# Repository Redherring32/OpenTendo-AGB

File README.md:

# OpenTendo Game Boy Advance (OpenGBA)

This is an open source recreation of the AGB-CPU-01 board. This was a joint effort between Redherring32 and Bucket Mouse (Mousebitelabs) - initial board scans, copper tracing, and footprint generation were done by Redherring32; schematic and symbol generation, PCB copper cleanup, and silkscreen were done by Bucket Mouse. This is a close to 1:1 recreation of the original AGB-CPU-01 circuit board - some liberties were taken here and there to ensure ease of manufacturability (namely, 6 mil spacing) and to improve aesthetics (most vias are *tented* rather than untented).

## File Structure

**Board Files**: contains the schematics and PCB files for KiCad 9.0

**Footprints/OpenTendo-AGB.pretty**: component footprints for KiCad 9.0

**Symbols**: component symbols for KiCad 9.0

**Bill_of_Materials.csv**: a list of components and component values for each part on the board (see [this site](https://docs.google.com/spreadsheets/d/17RfgOaR-P8M0cC5BojwuY52GbZUefLFm82To7ja963o/edit?gid=1605207223#gid=1605207223) for some alternatives)

**Gerbers.zip**: files used to order circuit boards from manufacturers (JLCPCB, PCBway, etc.)

## Board Characteristics and Order Information

The zipped folder contains all the gerber files for this board. The following options **must** be chosen when ordering boards for yourself.

- Thickness: 1.0mm
- Surface Finish: ENIG

## License
<br />This work is licensed under a <a rel="license" href="http://creativecommons.org/licenses/by-sa/4.0/">Creative Commons Attribution-ShareAlike 4.0 International License</a>. You are able to copy and redistribute the material in any medium or format, as well as remix, transform, or build upon the material for any purpose (even commercial) - but you **must** give appropriate credit, provide a link to the license, and indicate if any changes were made.

©Redherring32 2023-2026

©MouseBiteLabs 2026

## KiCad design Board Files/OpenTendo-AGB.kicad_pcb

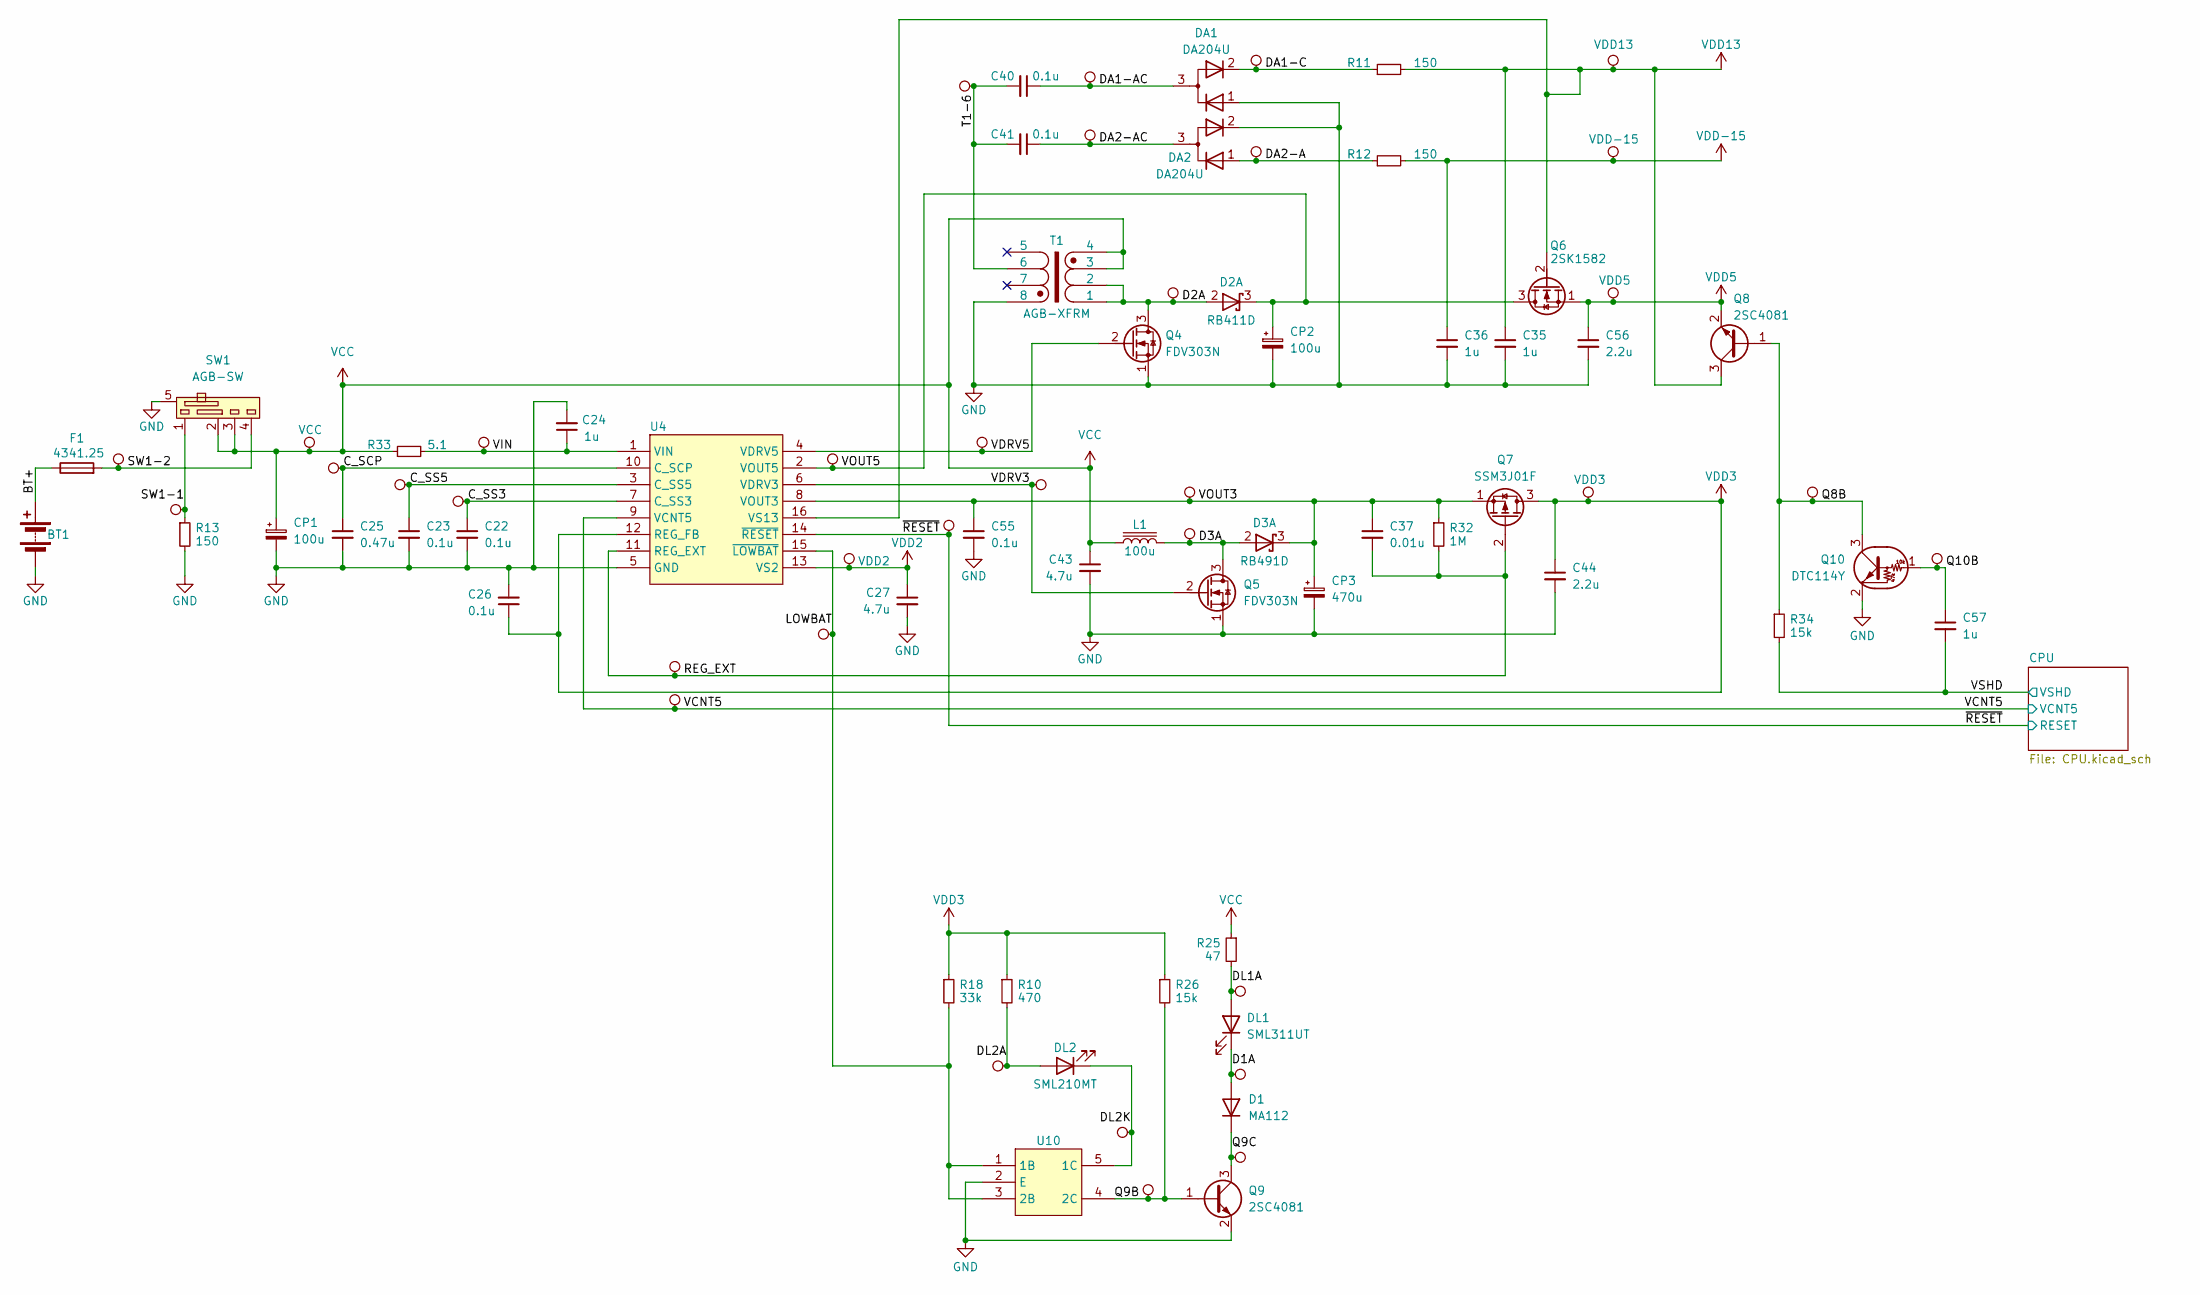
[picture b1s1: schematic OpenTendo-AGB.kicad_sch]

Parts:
BT1: Battery
C22, C23, C26, C40, C41, C55: 0.1u; C_0402_1005Metric
C24, C57: 1u; C_0603_1608Metric
C25: 0.47u; C_0603_1608Metric
C27, C43: 4.7u; C_0805_2012Metric
C35, C36: 1u; C_0805_2012Metric
C37: 0.01u; C_0402_1005Metric
C44, C56: 2.2u; C_0805_2012Metric
CP1: 100u; CP_Elec_5x5.3
CP2: 100u; C_Elec_6.3x5.8
CP3: 470u; C_Elec_8x10.2
D1: MA112; Diode
D2: RB411D; SOT-23
D3: RB491D; SOT-23
DA1, DA2: DA204U; SOT-323
DL1: SML311UT; LED_0603_1608Metric
DL2: SML210MT; LED_0603_1608Metric
F1: 4341.25; Fuse_0603_1608Metric
L1: 100u; Inductor
Q4, Q5: FDV303N; SOT-23
Q6: 2SK1582; SOT-23
Q7: SSM3J01F; SOT-23
Q8, Q9: 2SC4081; SOT-323
Q10: DTC114Y; SOT-323
R10: 470; R_0402_1005Metric
R11, R12, R13: 150; R_0402_1005Metric
R18: 33k; R_0402_1005Metric
R25: 47; R_0402_1005Metric
R26, R34: 15k; R_0402_1005Metric
R32: 1M; R_0402_1005Metric
R33: 5.1; R_0402_1005Metric
SW1: AGB-SW; Power Switch
T1: AGB-XFRM; Coil
TP10: VOUT3; TestPoint_Pad_D1.0mm_VIA
TP11: VDRV3; TestPoint_Pad_D1.0mm
TP12: VDD2; TestPoint_Pad_D0.8mm
TP13: VDRV5; TestPoint_Pad_D1.0mm
TP14: VOUT5; TestPoint_Pad_D0.8mm
TP15: ~{RESET}; TestPoint_Pad_D1.25mm_VIA
TP16: D3A; TestPoint_Pad_D1.0mm
TP17: D2A; TestPoint_Pad_D1.0mm_VIA
TP18: DA2-AC; TestPoint_Pad_D0.8mm_VIA
TP19: DA1-AC; TestPoint_Pad_D1.0mm_VIA
TP20: DA2-A; TestPoint_Pad_D0.8mm
TP21: DA1-C; TestPoint_Pad_D0.8mm
TP22: VDD13; TestPoint_Pad_D0.8mm
TP23: VDD-15; TestPoint_Pad_D1.0mm
TP24: VDD5; TestPoint_Pad_D1.0mm
TP25: Q8B; TestPoint_Pad_D0.8mm
TP27: Q10B; TestPoint_Pad_D0.8mm_VIA
TP28: LOWBAT; TestPoint_Pad_D0.8mm
TP29: DL2A; TestPoint_Pad_D0.8mm_VIA
TP30: DL2K; TestPoint_Pad_D0.8mm_VIA
TP31: DL1A; TestPoint_Pad_D0.8mm_VIA
TP32: D1A; TestPoint_Pad_D0.8mm_VIA
TP33: Q9C; TestPoint_Pad_D1.0mm
TP34: Q9B; TestPoint_Pad_D0.8mm
TP83: SW1-2; TestPoint_Pad_D1.25mm
TP84: SW1-1; TestPoint_Pad_D0.8mm
TP85: VCC; TestPoint_Pad_D0.8mm
TP86: C_SCP; TestPoint_Pad_D1.0mm
TP87: C_SS5; TestPoint_Pad_D1.0mm
TP88: C_SS3; TestPoint_Pad_D1.0mm
TP89: VIN; TestPoint_Pad_D0.8mm_VIA
TP90: REG_EXT; TestPoint_Pad_D0.8mm
TP91: VCNT5; TestPoint_Pad_D1.0mm
TP113: VDD3; TestPoint_Pad_D0.8mm
TP116: T1-6; TestPoint_Pad_D1.0mm_VIA
U4: AGB-PMIC; TSSOP-16_4.4x5mm_P0.65mm
U10: UMG3N; SOT-353_SC-70-5

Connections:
/BT+: BT1.1 (+), F1.1
/C_SCP: C25.1, TP86.1, U4.10 (C_SCP)
/C_SS3: C22.1, TP88.1, U4.7 (C_SS3)
/C_SS5: C23.1, TP87.1, U4.3 (C_SS5)
/D1A: D1.2 (A), DL1.1 (K), TP32.1
/D2A: D2.2 (A), Q4.3 (D), T1.1, T1.2, TP17.1
/D3A: D3.2 (A), L1.2, Q5.3 (D), TP16.1
/DA1-AC: C40.1, DA1.3 (common), TP19.1
/DA1-C: DA1.2 (K), R11.1, TP21.1
/DA2-A: DA2.1 (A), R12.1, TP20.1
/DA2-AC: C41.1, DA2.3 (common), TP18.1
/DL1A: DL1.2 (A), R25.2, TP31.1
/DL2A: DL2.2 (A), R10.2, TP29.1
/DL2K: DL2.1 (K), TP30.1, U10.5 (1C)
/LOWBAT: R18.2, TP28.1, U4.15 (~LOWBAT), U10.1 (1B), U10.3 (2B)
/Q8B: Q8.1 (B), Q10.3 (C), R34.1, TP25.1
/Q9B: Q9.1 (B), R26.2, TP34.1, U10.4 (2C)
/Q9C: D1.1 (K), Q9.3 (C), TP33.1
/Q10B: C57.1, Q10.1 (B), TP27.1
/REG_EXT: C37.2, Q7.2 (G), R32.2, TP90.1, U4.11 (REG_EXT)
/SW1-1: R13.1, SW1.1, TP84.1
/SW1-2: F1.2, SW1.4 (2), TP83.1
/T1-6: C40.2, C41.2, T1.6, TP116.1
/VCNT5: TP91.1, U4.9 (VCNT5); also elsewhere on the board
/VDRV3: Q5.2 (G), TP11.1, U4.6 (VDRV3)
/VDRV5: Q4.2 (G), TP13.1, U4.4 (VDRV5)
/VIN: C24.1, R33.2, TP89.1, U4.1 (VIN)
/VOUT3: C37.1, C55.1, CP3.1, D3.3 (K), Q7.1 (S), R32.1, TP10.1, U4.8 (VOUT3)
/VOUT5: CP2.1, D2.3 (K), Q6.3 (D), TP14.1, U4.2 (VOUT5)
/VSHD: C57.2, R34.2; also elsewhere on the board
/~RESET: TP15.1, U4.14 (~RESET); also elsewhere on the board
GND: BT1.2 (-), C22.2, C23.2, C24.2, C25.2, C26.2, C27.2, C35.2, C36.2, C43.2, C44.2, C55.2, C56.2, CP1.2, CP2.2, CP3.2, DA1.1 (A), DA2.2 (K), Q4.1 (S), Q5.1 (S), Q9.2 (E), Q10.2 (E), R13.2, SW1.5 (SH), T1.8, U4.5 (GND), U10.2 (E); also elsewhere on the board
VCC: C43.1, CP1.1, L1.1, R25.1, R33.1, SW1.2 (C), SW1.3 (C), T1.3, T1.4, TP85.1; also elsewhere on the board
VDD2: C27.1, TP12.1, U4.13 (VS2); also elsewhere on the board
VDD3: C26.1, C44.1, Q7.3 (D), R10.1, R18.1, R26.1, TP113.1, U4.12 (REG_FB); also elsewhere on the board
VDD5: C56.1, Q6.1 (S), Q8.2 (E), TP24.1; also elsewhere on the board
VDD13: C35.1, Q6.2 (G), Q8.3 (C), R11.2, TP22.1, U4.16 (VS13); also elsewhere on the board
VDD-15: C36.1, R12.2, TP23.1; also elsewhere on the board

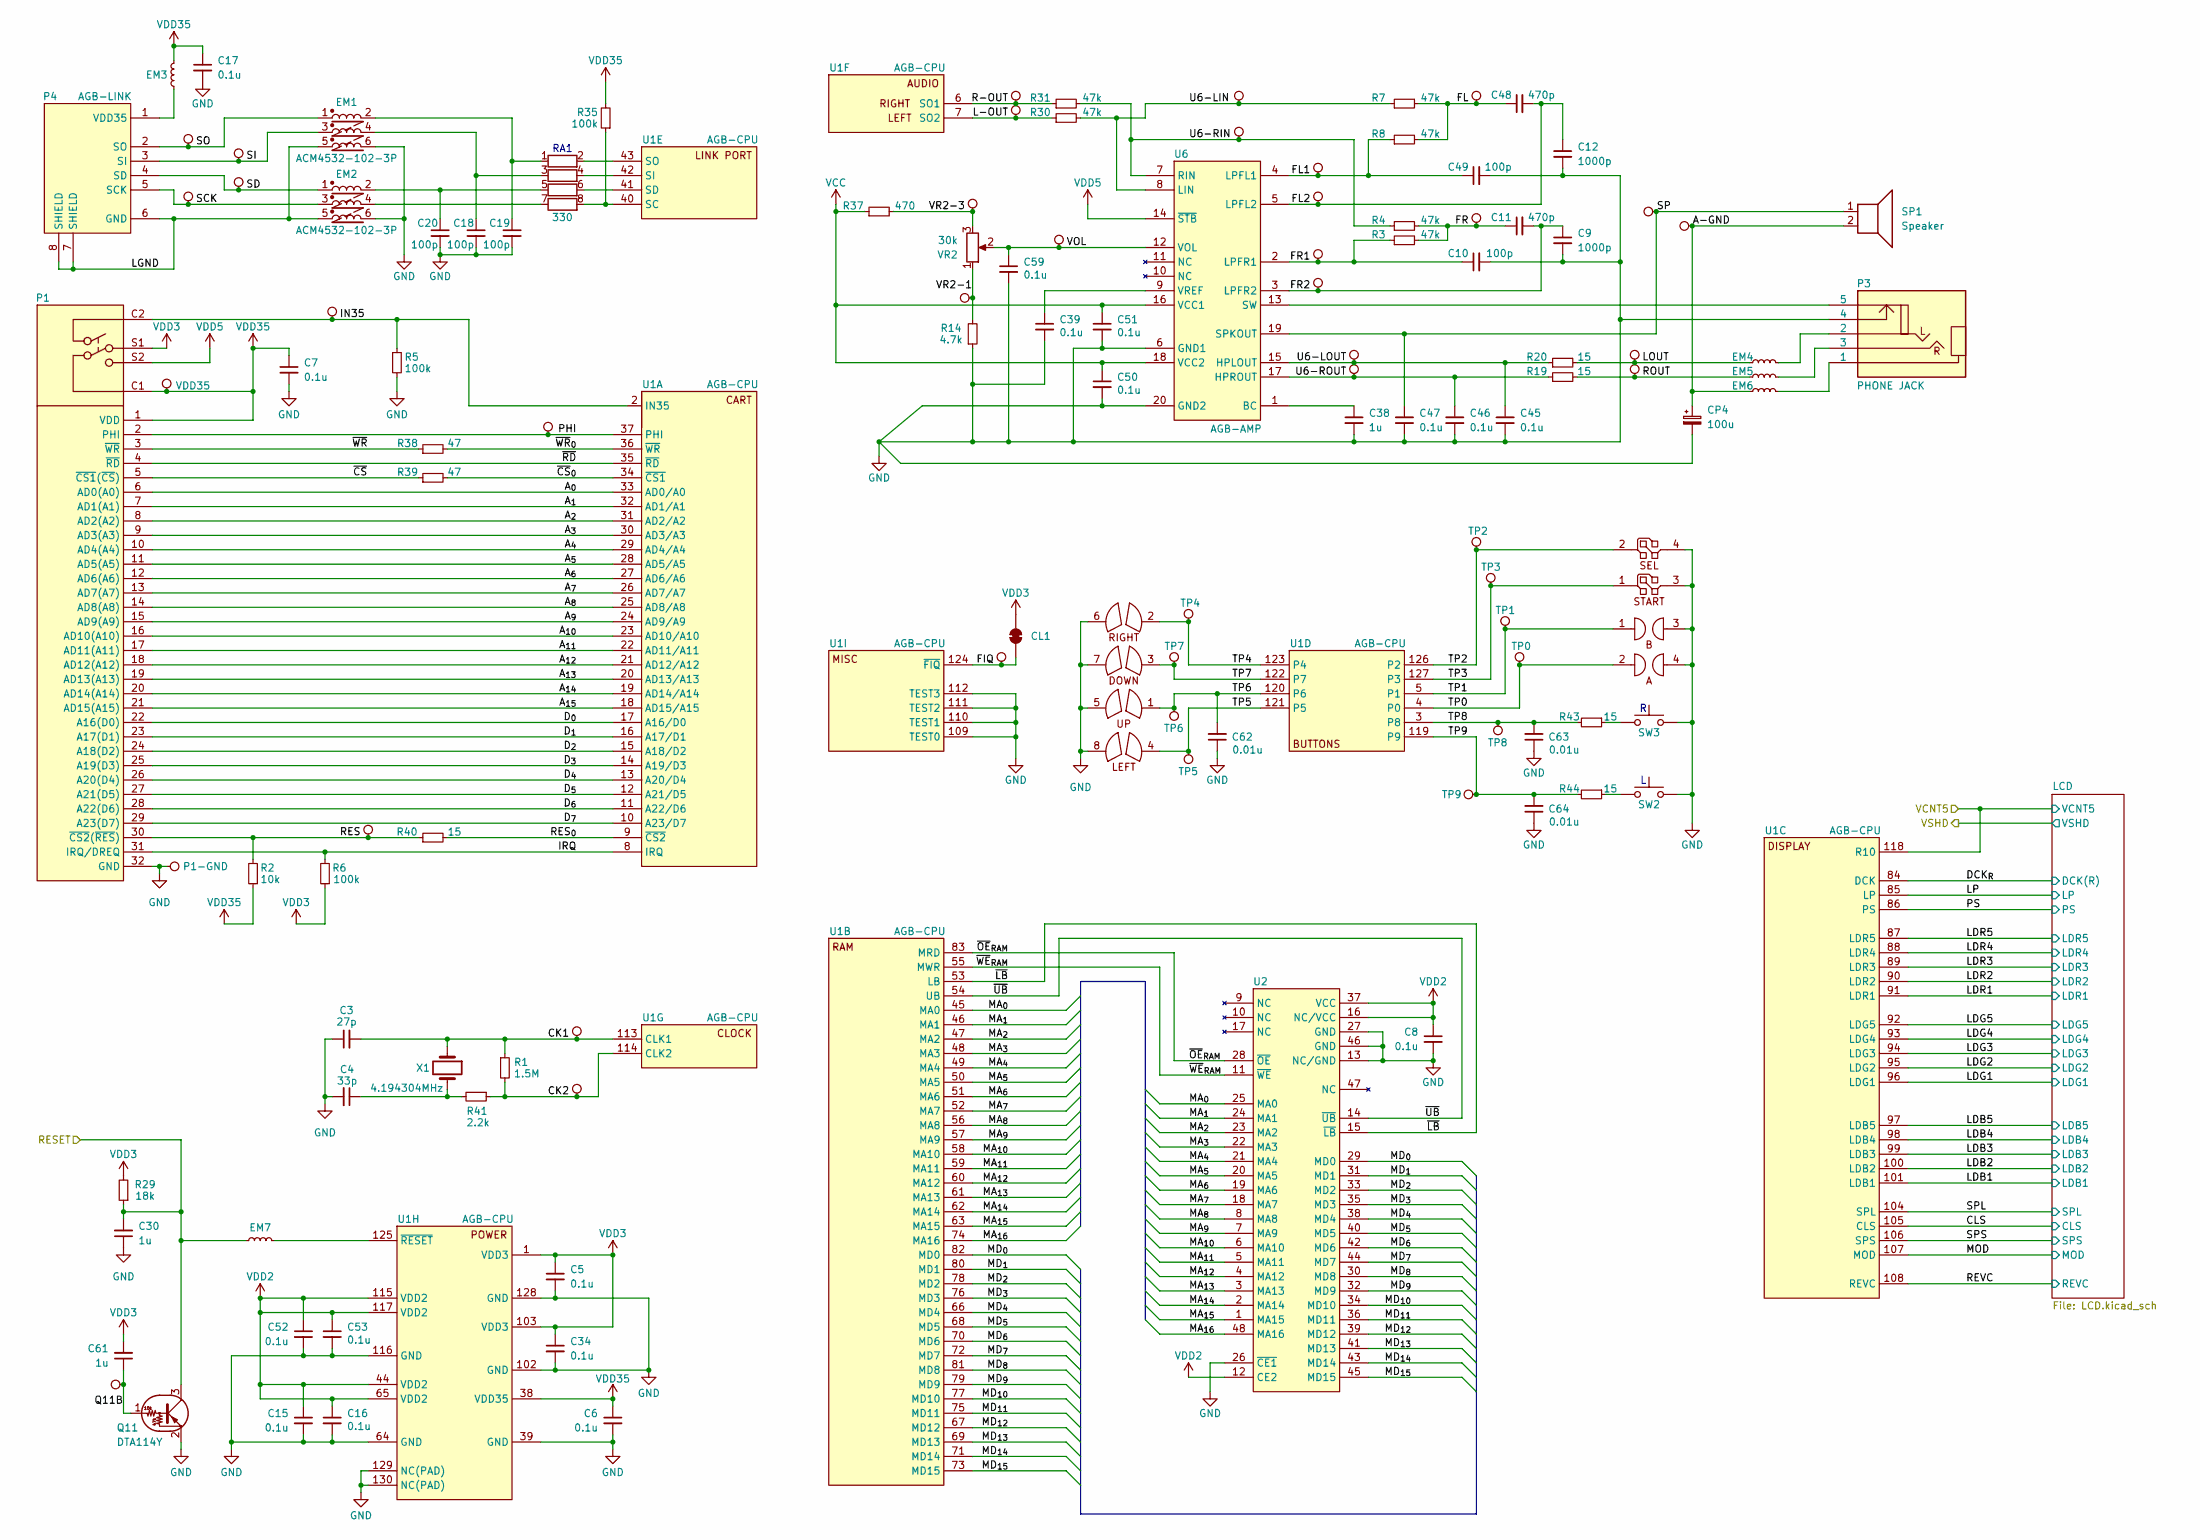
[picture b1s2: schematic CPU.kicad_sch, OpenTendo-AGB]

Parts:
C3: 27p; C_0402_1005Metric
C4: 33p; C_0402_1005Metric
C5, C6, C7, C8, C15, C16, C17, C34, C39, C45, C46, C47, C50, C51, C52, C53, C59: 0.1u; C_0402_1005Metric
C9, C12: 1000p; C_0402_1005Metric
C10, C18, C19, C20, C49: 100p; C_0402_1005Metric
C11, C48: 470p; C_0402_1005Metric
C30, C38, C61: 1u; C_0603_1608Metric
C62, C63, C64: 0.01u; C_0402_1005Metric
CL1: SolderJumper_2_Bridged; Jumper-Bridged
CP4: 100u; CP_Elec_5x5.3
EM1, EM2: ACM4532-102-3P; EM
EM3, EM7: HW601; L_0603_1608Metric
EM4, EM5, EM6: BLM11B252SD; L_0603_1608Metric
P1: CART; CartSlot
P3: PHONE JACK; Audio-Jack
P4: AGB-LINK; EXT
Q11: DTA114Y; SOT-323
R1: 1.5M; R_0402_1005Metric
R2: 10k; R_0402_1005Metric
R3, R4, R7, R8, R30, R31: 47k; R_0402_1005Metric
R5, R6, R35: 100k; R_0402_1005Metric
R14: 4.7k; R_0402_1005Metric
R19, R20, R40, R43, R44: 15; R_0402_1005Metric
R29: 18k; R_0402_1005Metric
R37: 470; R_0402_1005Metric
R38, R39: 47; R_0402_1005Metric
R41: 2.2k; R_0402_1005Metric
RA1: 330; RA
SP1: Speaker
SW2: SW_Push; L
SW3: SW_Push; R
SW4: AGB-A-B; AB
SW5: AGB-ST-SEL; StartSelect
SW6: AGB-DPAD; DPAD
TP0: TP0; TestPoint_Pad_D1.0mm
TP1: TP1; TestPoint_Pad_D1.0mm
TP2: TP2; TestPoint_Pad_D0.8mm
TP3: TP3; TestPoint_Pad_D0.8mm
TP4: TP4; TestPoint_Pad_D0.8mm
TP5: TP5; TestPoint_Pad_D1.0mm
TP6: TP6; TestPoint_Pad_D0.8mm
TP7: TP7; TestPoint_Pad_D1.0mm
TP8: TP8; TestPoint_Pad_D0.8mm_VIA
TP9: TP9; TestPoint_Pad_D0.8mm
TP35: Q11B; TestPoint_Pad_D0.8mm_VIA
TP75: IN35; TestPoint_Pad_D1.0mm_VIA
TP76: VDD35; TestPoint_Pad_D1.0mm
TP77: PHI; TestPoint_Pad_D1.0mm
TP78: RES; TestPoint_Pad_D0.8mm_VIA
TP79: P1-GND; TestPoint_Pad_D1.0mm
TP80: CK1; TestPoint_Pad_D0.8mm
TP81: CK2; TestPoint_Pad_D0.8mm
TP82: FIQ; TestPoint_Pad_D1.25mm_VIA
TP92: SO; TestPoint_Pad_D0.8mm
TP93: SD; TestPoint_Pad_D0.8mm_VIA
TP94: SI; TestPoint_Pad_D0.8mm
TP95: SCK; TestPoint_Pad_D0.8mm_VIA
TP96: U6-LIN; TestPoint_Pad_D0.8mm
TP97: U6-RIN; TestPoint_Pad_D0.8mm
TP98: FL; TestPoint_Pad_D0.8mm
TP99: FR; TestPoint_Pad_D0.8mm
TP100: FL1; TestPoint_Pad_D0.8mm
TP101: FL2; TestPoint_Pad_D0.8mm
TP102: FR1; TestPoint_Pad_D0.8mm
TP103: FR2; TestPoint_Pad_D0.8mm
TP104: U6-LOUT; TestPoint_Pad_D0.8mm_VIA
TP105: U6-ROUT; TestPoint_Pad_D0.8mm
TP106: VOL; TestPoint_Pad_D0.8mm_VIA
TP107: VR2-3; TestPoint_Pad_D0.8mm_VIA
TP108: VR2-1; TestPoint_Pad_D0.8mm_VIA
TP109: LOUT; TestPoint_Pad_D0.8mm
TP110: ROUT; TestPoint_Pad_D0.8mm
TP111: SP; TestPoint_Pad_D1.25mm_VIA
TP112: A-GND; TestPoint_Pad_D1.0mm
TP114: R-OUT; TestPoint_Pad_D0.8mm
TP115: L-OUT; TestPoint_Pad_D0.8mm
U1: AGB-CPU; CPU-AGB
U2: AGB-SRAM
U6: AGB-AMP
VR2: 30k; Thumbwheel
X1: 4.194304MHz; Crystal

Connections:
/CPU/A-GND: CP4.1, EM6.1, SP1.2, TP112.1
/CPU/A_{0}: P1.6 (AD0(A0)), U1.33 (AD0/A0)
/CPU/A_{1}: P1.7 (AD1(A1)), U1.32 (AD1/A1)
/CPU/A_{2}: P1.8 (AD2(A2)), U1.31 (AD2/A2)
/CPU/A_{3}: P1.9 (AD3(A3)), U1.30 (AD3/A3)
/CPU/A_{4}: P1.10 (AD4(A4)), U1.29 (AD4/A4)
/CPU/A_{5}: P1.11 (AD5(A5)), U1.28 (AD5/A5)
/CPU/A_{6}: P1.12 (AD6(A6)), U1.27 (AD6/A6)
/CPU/A_{7}: P1.13 (AD7(A7)), U1.26 (AD7/A7)
/CPU/A_{8}: P1.14 (AD8(A8)), U1.25 (AD8/A8)
/CPU/A_{9}: P1.15 (AD9(A9)), U1.24 (AD9/A9)
/CPU/A_{10}: P1.16 (AD10(A10)), U1.23 (AD10/A10)
/CPU/A_{11}: P1.17 (AD11(A11)), U1.22 (AD11/A11)
/CPU/A_{12}: P1.18 (AD12(A12)), U1.21 (AD12/A12)
/CPU/A_{13}: P1.19 (AD13(A13)), U1.20 (AD13/A13)
/CPU/A_{14}: P1.20 (AD14(A14)), U1.19 (AD14/A14)
/CPU/A_{15}: P1.21 (AD15(A15)), U1.18 (AD15/A15)
/CPU/CK1: C3.2, R1.1, TP80.1, U1.113 (CLK1), X1.1
/CPU/CK2: R1.2, R41.1, TP81.1, U1.114 (CLK2)
/CPU/CLS: U1.105 (CLS); also elsewhere on the board
/CPU/DCK_{R}: U1.84 (DCK); also elsewhere on the board
/CPU/D_{0}: P1.22 (A16(D0)), U1.17 (A16/D0)
/CPU/D_{1}: P1.23 (A17(D1)), U1.16 (A17/D1)
/CPU/D_{2}: P1.24 (A18(D2)), U1.15 (A18/D2)
/CPU/D_{3}: P1.25 (A19(D3)), U1.14 (A19/D3)
/CPU/D_{4}: P1.26 (A20(D4)), U1.13 (A20/D4)
/CPU/D_{5}: P1.27 (A21(D5)), U1.12 (A21/D5)
/CPU/D_{6}: P1.28 (A22(D6)), U1.11 (A22/D6)
/CPU/D_{7}: P1.29 (A23(D7)), U1.10 (A23/D7)
/CPU/FIQ: CL1.1 (A), TP82.1, U1.124 (~FIQ)
/CPU/FL: C48.1, R7.2, R8.2, TP98.1
/CPU/FL1: C49.1, R8.1, TP100.1, U6.4 (LPFL1)
/CPU/FL2: C12.1, C48.2, TP101.1, U6.5 (LPFL2)
/CPU/FR: C11.1, R3.2, R4.2, TP99.1
/CPU/FR1: C10.1, R3.1, TP102.1, U6.2 (LPFR1)
/CPU/FR2: C9.1, C11.2, TP103.1, U6.3 (LPFR2)
/CPU/IN35: P1.C2, R5.1, TP75.1, U1.2 (IN35)
/CPU/IRQ: P1.31 (IRQ/DREQ), R6.2, U1.8 (IRQ)
/CPU/L-OUT: R30.1, TP115.1, U1.7 (SO2)
/CPU/LDB1: U1.101 (LDB1); also elsewhere on the board
/CPU/LDB2: U1.100 (LDB2); also elsewhere on the board
/CPU/LDB3: U1.99 (LDB3); also elsewhere on the board
/CPU/LDB4: U1.98 (LDB4); also elsewhere on the board
/CPU/LDB5: U1.97 (LDB5); also elsewhere on the board
/CPU/LDG1: U1.96 (LDG1); also elsewhere on the board
/CPU/LDG2: U1.95 (LDG2); also elsewhere on the board
/CPU/LDG3: U1.94 (LDG3); also elsewhere on the board
/CPU/LDG4: U1.93 (LDG4); also elsewhere on the board
/CPU/LDG5: U1.92 (LDG5); also elsewhere on the board
/CPU/LDR1: U1.91 (LDR1); also elsewhere on the board
/CPU/LDR2: U1.90 (LDR2); also elsewhere on the board
/CPU/LDR3: U1.89 (LDR3); also elsewhere on the board
/CPU/LDR4: U1.88 (LDR4); also elsewhere on the board
/CPU/LDR5: U1.87 (LDR5); also elsewhere on the board
/CPU/LGND: EM1.5, EM2.5, P4.6 (GND), P4.7 (SHIELD), P4.8 (SHIELD)
/CPU/LOUT: EM4.1, R20.2, TP109.1
/CPU/LP: U1.85 (LP); also elsewhere on the board
/CPU/MA_{0}: U1.45 (MA0), U2.25 (MA0)
/CPU/MA_{1}: U1.46 (MA1), U2.24 (MA1)
/CPU/MA_{2}: U1.47 (MA2), U2.23 (MA2)
/CPU/MA_{3}: U1.48 (MA3), U2.22 (MA3)
/CPU/MA_{4}: U1.49 (MA4), U2.21 (MA4)
/CPU/MA_{5}: U1.50 (MA5), U2.20 (MA5)
/CPU/MA_{6}: U1.51 (MA6), U2.19 (MA6)
/CPU/MA_{7}: U1.52 (MA7), U2.18 (MA7)
/CPU/MA_{8}: U1.56 (MA8), U2.8 (MA8)
/CPU/MA_{9}: U1.57 (MA9), U2.7 (MA9)
/CPU/MA_{10}: U1.58 (MA10), U2.6 (MA10)
/CPU/MA_{11}: U1.59 (MA11), U2.5 (MA11)
/CPU/MA_{12}: U1.60 (MA12), U2.4 (MA12)
/CPU/MA_{13}: U1.61 (MA13), U2.3 (MA13)
/CPU/MA_{14}: U1.62 (MA14), U2.2 (MA14)
/CPU/MA_{15}: U1.63 (MA15), U2.1 (MA15)
/CPU/MA_{16}: U1.74 (MA16), U2.48 (MA16)
/CPU/MD_{0}: U1.82 (MD0), U2.29 (MD0)
/CPU/MD_{1}: U1.80 (MD1), U2.31 (MD1)
/CPU/MD_{2}: U1.78 (MD2), U2.33 (MD2)
/CPU/MD_{3}: U1.76 (MD3), U2.35 (MD3)
/CPU/MD_{4}: U1.66 (MD4), U2.38 (MD4)
/CPU/MD_{5}: U1.68 (MD5), U2.40 (MD5)
/CPU/MD_{6}: U1.70 (MD6), U2.42 (MD6)
/CPU/MD_{7}: U1.72 (MD7), U2.44 (MD7)
/CPU/MD_{8}: U1.81 (MD8), U2.30 (MD8)
/CPU/MD_{9}: U1.79 (MD9), U2.32 (MD9)
/CPU/MD_{10}: U1.77 (MD10), U2.34 (MD10)
/CPU/MD_{11}: U1.75 (MD11), U2.36 (MD11)
/CPU/MD_{12}: U1.67 (MD12), U2.39 (MD12)
/CPU/MD_{13}: U1.69 (MD13), U2.41 (MD13)
/CPU/MD_{14}: U1.71 (MD14), U2.43 (MD14)
/CPU/MD_{15}: U1.73 (MD15), U2.45 (MD15)
/CPU/MOD: U1.107 (MOD); also elsewhere on the board
/CPU/PHI: P1.2 (PHI), TP77.1, U1.37 (PHI)
/CPU/PS: U1.86 (PS); also elsewhere on the board
/CPU/Q11B: C61.1, Q11.1 (B), TP35.1
/CPU/R-OUT: R31.1, TP114.1, U1.6 (SO1)
/CPU/RES: P1.30 (~CS2(~RES)), R2.2, R40.1, TP78.1
/CPU/RES_{0}: R40.2, U1.9 (~CS2)
/CPU/REVC: U1.108 (REVC); also elsewhere on the board
/CPU/ROUT: EM5.1, R19.2, TP110.1
/CPU/SCK: EM2.3, P4.5 (SCK), TP95.1
/CPU/SD: EM2.1, P4.4 (SD), TP93.1
/CPU/SI: EM1.3, P4.3 (SI), TP94.1
/CPU/SO: EM1.1, P4.2 (SO), TP92.1
/CPU/SP: C47.1, SP1.1, TP111.1, U6.19 (SPKOUT)
/CPU/SPL: U1.104 (SPL); also elsewhere on the board
/CPU/SPS: U1.106 (SPS); also elsewhere on the board
/CPU/TP0: SW4.2 (A), TP0.1, U1.4 (P0)
/CPU/TP1: SW4.1 (B), TP1.1, U1.5 (P1)
/CPU/TP2: SW5.2 (SEL), TP2.1, U1.126 (P2)
/CPU/TP3: SW5.1 (START), TP3.1, U1.127 (P3)
/CPU/TP4: SW6.2 (RIGHT), TP4.1, U1.123 (P4)
/CPU/TP5: SW6.4 (LEFT), TP5.1, U1.121 (P5)
/CPU/TP6: C62.2, SW6.1 (UP), TP6.1, U1.120 (P6)
/CPU/TP7: SW6.3 (DOWN), TP7.1, U1.122 (P7)
/CPU/TP8: C63.2, R43.2, TP8.1, U1.3 (P8)
/CPU/TP9: C64.2, R44.2, TP9.1, U1.119 (P9)
/CPU/U6-LIN: R7.1, R30.2, TP96.1, U6.8 (LIN)
/CPU/U6-LOUT: C45.1, R20.1, TP104.1, U6.15 (HPLOUT)
/CPU/U6-RIN: R4.1, R31.2, TP97.1, U6.7 (RIN)
/CPU/U6-ROUT: C46.1, R19.1, TP105.1, U6.17 (HPROUT)
/CPU/VOL: C59.1, TP106.1, U6.12 (VOL), VR2.2
/CPU/VR2-1: R14.2, TP108.1, VR2.1
/CPU/VR2-3: R37.2, TP107.1, VR2.3
/CPU/~CS: P1.5 (~CS1(~CS)), R39.1
/CPU/~CS_{0}: R39.2, U1.34 (~CS1)
/CPU/~LB: U1.53 (LB), U2.15 (~LB)
/CPU/~OE_{RAM}: U1.83 (MRD), U2.28 (~OE)
/CPU/~RD: P1.4 (~RD), U1.35 (~RD)
/CPU/~UB: U1.54 (UB), U2.14 (~UB)
/CPU/~WE_{RAM}: U1.55 (MWR), U2.11 (~WE)
/CPU/~WR: P1.3 (~WR), R38.1
/CPU/~WR_{0}: R38.2, U1.36 (~WR)
/VCNT5: U1.118 (R10); also elsewhere on the board
/~RESET: C30.2, EM7.1, Q11.3 (C), R29.1; also elsewhere on the board
GND: C3.1, C4.2, C5.2, C6.2, C7.2, C8.2, C9.2, C10.2, C12.2, C15.2, C16.2, C17.2, C18.2, C19.2, C20.2, C30.1, C34.2, C38.2, C39.2, C45.2, C46.2, C47.2, C49.2, C50.2, C51.2, C52.2, C53.2, C59.2, C62.1, C63.1, C64.1, CP4.2, EM1.6, EM2.6, P1.32 (GND), P3.4, Q11.2 (E), R5.2, R14.1, SW2.2, SW3.2, SW4.3 (GND), SW4.4 (GND), SW5.3 (GND), SW5.4 (GND), SW6.5 (GND), SW6.6 (GND), SW6.7 (GND), SW6.8 (GND), TP79.1, U1.39 (GND), U1.64 (GND), U1.102 (GND), U1.109 (TEST0), U1.110 (TEST1), U1.111 (TEST2), U1.112 (TEST3), U1.116 (GND), U1.128 (GND), U1.129 (NC(PAD)), U1.130 (NC(PAD)), U2.13 (NC/GND), U2.26 (~CE1), U2.27 (GND), U2.46 (GND), U6.6 (GND1), U6.20 (GND2); also elsewhere on the board
unnamed: C4.1, R41.2, X1.2
unnamed: EM4.2, P3.2
unnamed: EM5.2, P3.3
unnamed: EM6.2, P3.1
unnamed: EM3.2, P4.1 (VDD35)
unnamed: R43.1, SW3.1
unnamed: R44.1, SW2.1
unnamed: C19.1, EM1.2, RA1.1 (R1.1)
unnamed: RA1.2 (R1.2), U1.43 (SO)
unnamed: C18.1, EM1.4, RA1.3 (R2.1)
unnamed: RA1.4 (R2.2), U1.42 (SI)
unnamed: C20.1, EM2.2, RA1.5 (R3.1)
unnamed: RA1.6 (R3.2), U1.41 (SD)
unnamed: EM2.4, RA1.7 (R4.1)
unnamed: R35.1, RA1.8 (R4.2), U1.40 (SC)
unnamed: EM7.2, U1.125 (~RESET)
unnamed: C38.1, U6.1 (BC)
unnamed: P3.5, U6.13 (SW)
unnamed: C39.1, U6.9 (VREF)
VCC: C50.1, C51.1, R37.1, U6.16 (VCC1), U6.18 (VCC2); also elsewhere on the board
VDD2: C8.1, C15.1, C16.1, C52.1, C53.1, U1.44 (VDD2), U1.65 (VDD2), U1.115 (VDD2), U1.117 (VDD2), U2.12 (CE2), U2.16 (NC/VCC), U2.37 (VCC); also elsewhere on the board
VDD3: C5.1, C34.1, C61.2, CL1.2 (B), P1.S1, R6.1, R29.2, U1.1 (VDD3), U1.103 (VDD3); also elsewhere on the board
VDD5: P1.S2, U6.14 (~STB); also elsewhere on the board
VDD35: C6.1, C7.1, C17.1, EM3.1, P1.1 (VDD), P1.C1, R2.1, R35.2, TP76.1, U1.38 (VDD35)

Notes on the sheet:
RA1

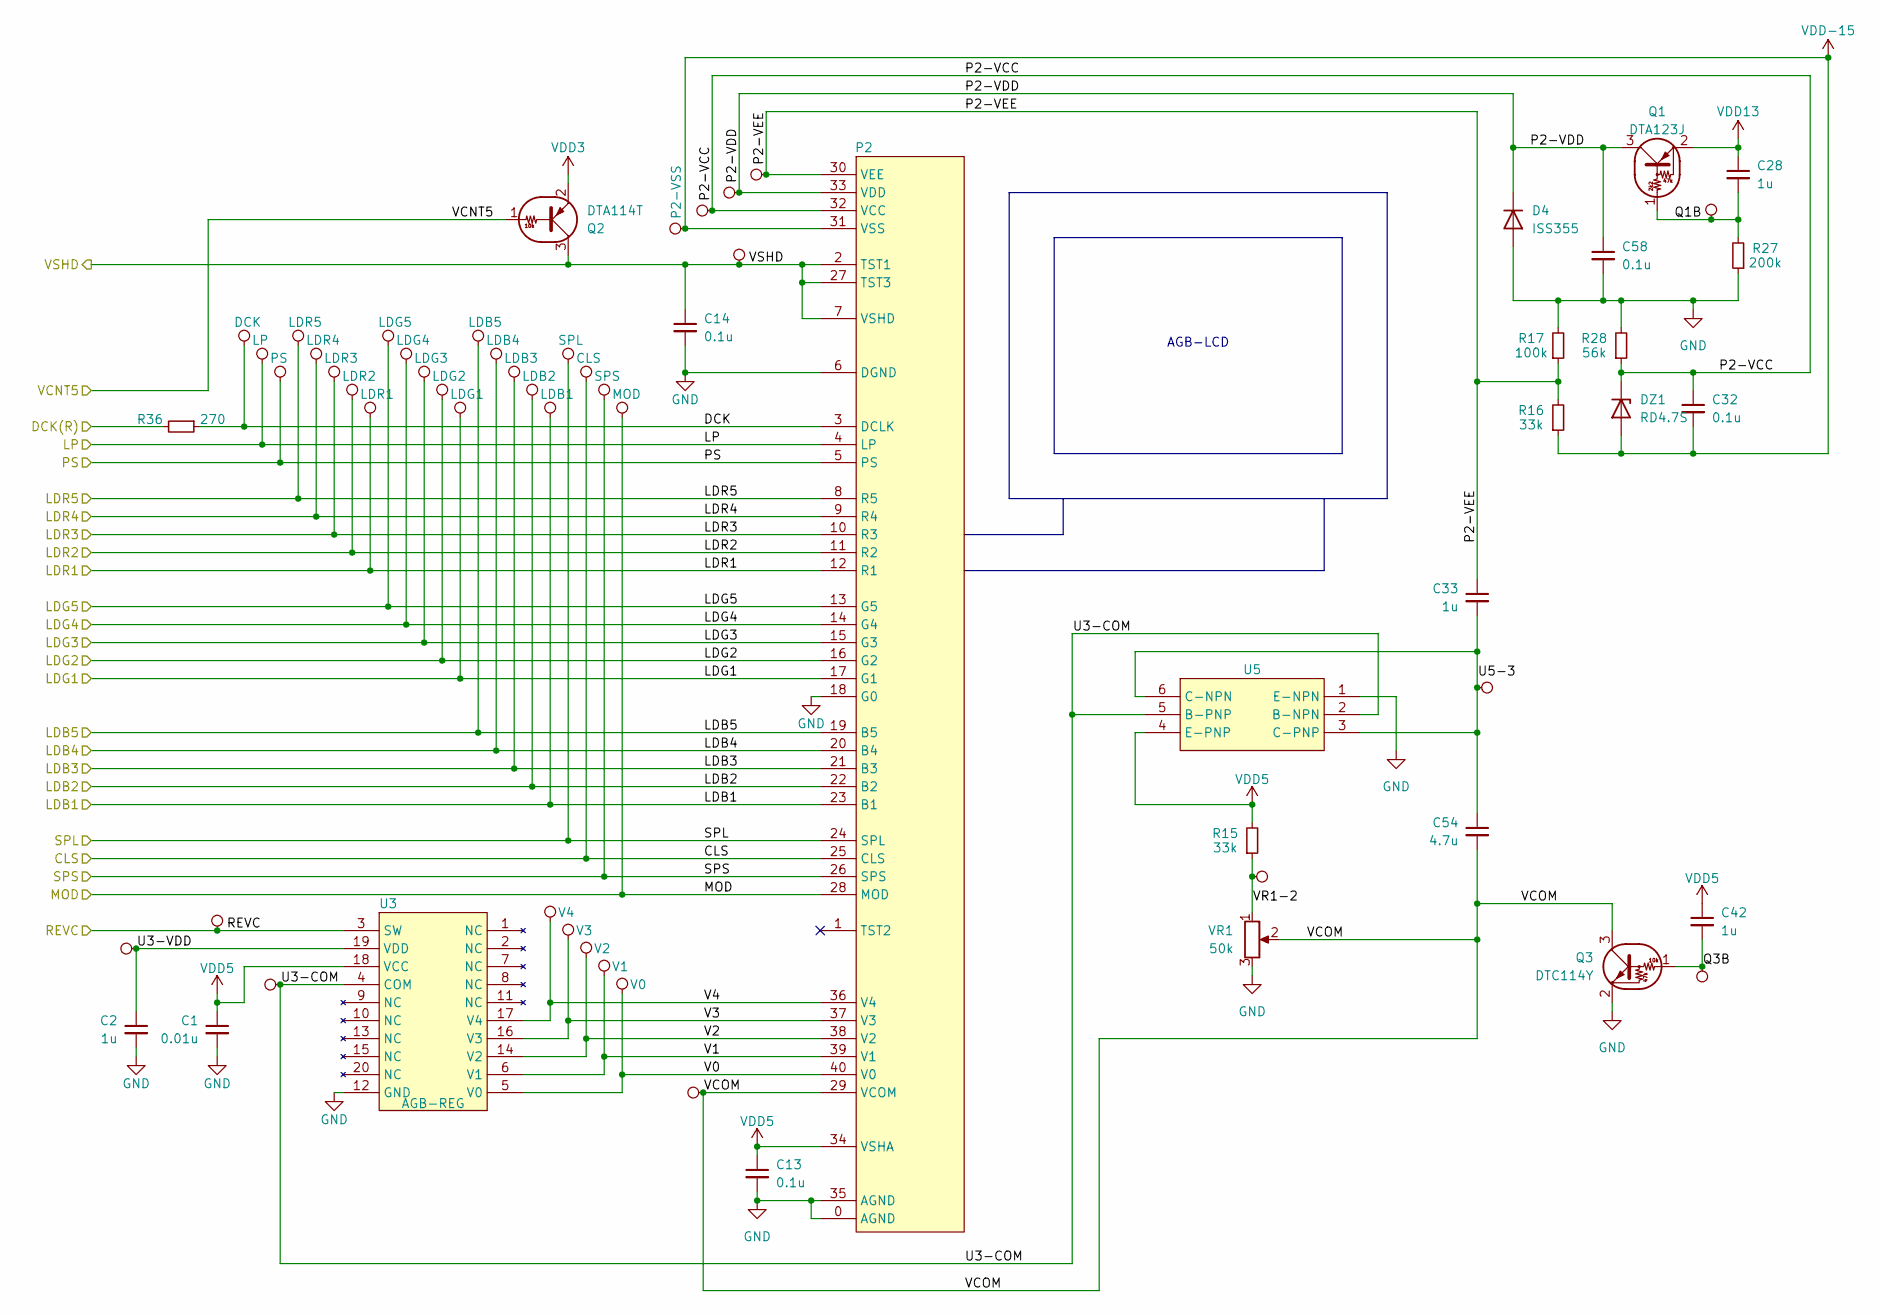
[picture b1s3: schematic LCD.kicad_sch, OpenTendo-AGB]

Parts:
C1: 0.01u; C_0402_1005Metric
C2, C28, C42: 1u; C_0603_1608Metric
C13, C14, C32, C58: 0.1u; C_0402_1005Metric
C33: 1u; C_0805_2012Metric
C54: 4.7u; C_0805_2012Metric
D4: ISS355; Diode
DZ1: RD4.7S; Diode
P2: LCD; LCD-Connector
Q1: DTA123J; SOT-323
Q2: DTA114T; SOT-323
Q3: DTC114Y; SOT-323
R15, R16: 33k; R_0402_1005Metric
R17: 100k; R_0402_1005Metric
R27: 200k; R_0402_1005Metric
R28: 56k; R_0402_1005Metric
R36: 270; R_0402_1005Metric
TP26: VSHD; TestPoint_Pad_D0.8mm
TP36: MOD; TestPoint_Pad_D0.8mm_VIA
TP37: SPS; TestPoint_Pad_D0.8mm_VIA
TP38: CLS; TestPoint_Pad_D0.8mm_VIA
TP39: SPL; TestPoint_Pad_D0.8mm_VIA
TP40: LDB1; TestPoint_Pad_D0.8mm_VIA
TP41: LDB2; TestPoint_Pad_D0.8mm_VIA
TP42: LDB3; TestPoint_Pad_D0.8mm_VIA
TP43: LDB4; TestPoint_Pad_D0.8mm_VIA
TP44: LDB5; TestPoint_Pad_D0.8mm_VIA
TP45: LDG1; TestPoint_Pad_D0.8mm_VIA
TP46: LDG2; TestPoint_Pad_D0.8mm_VIA
TP47: LDG3; TestPoint_Pad_D0.8mm_VIA
TP48: LDG4; TestPoint_Pad_D0.8mm_VIA
TP49: LDG5; TestPoint_Pad_D0.8mm_VIA
TP50: LDR1; TestPoint_Pad_D0.8mm_VIA
TP51: LDR2; TestPoint_Pad_D0.8mm_VIA
TP52: LDR3; TestPoint_Pad_D0.8mm_VIA
TP53: LDR4; TestPoint_Pad_D0.8mm_VIA
TP54: LDR5; TestPoint_Pad_D0.8mm_VIA
TP55: PS; TestPoint_Pad_D0.8mm_VIA
TP56: LP; TestPoint_Pad_D0.8mm_VIA
TP57: DCK; TestPoint_Pad_D0.8mm
TP58: P2-VSS; TestPoint_Pad_D0.8mm
TP59: P2-VCC; TestPoint_Pad_D0.8mm
TP60: P2-VDD; TestPoint_Pad_D0.8mm_VIA
TP61: P2-VEE; TestPoint_Pad_D0.8mm_VIA
TP62: REVC; TestPoint_Pad_D0.8mm
TP63: U3-VDD; TestPoint_Pad_D0.8mm
TP64: V0; TestPoint_Pad_D0.8mm
TP65: V1; TestPoint_Pad_D0.8mm
TP66: V2; TestPoint_Pad_D0.8mm
TP67: V3; TestPoint_Pad_D0.8mm_VIA
TP68: V4; TestPoint_Pad_D0.8mm
TP69: U3-COM; TestPoint_Pad_D0.8mm
TP70: VCOM; TestPoint_Pad_D0.8mm_VIA
TP71: VR1-2; TestPoint_Pad_D0.8mm_VIA
TP72: U5-3; TestPoint_Pad_D0.8mm_VIA
TP73: Q3B; TestPoint_Pad_D0.8mm_VIA
TP74: Q1B; TestPoint_Pad_D0.8mm_VIA
U3: AGB-REG
U5: UMD2N; SOT-363_SC-70-6
VR1: 50k; VR1

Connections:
/CPU/CLS: P2.25 (CLS), TP38.1; also elsewhere on the board
/CPU/DCK_{R}: R36.2; also elsewhere on the board
/CPU/LCD/DCK: P2.3 (DCLK), R36.1, TP57.1
/CPU/LCD/P2-VCC: C32.1, DZ1.1 (K), P2.32 (VCC), R28.1, TP59.1
/CPU/LCD/P2-VDD: C58.1, D4.1 (K), P2.33 (VDD), Q1.3 (C), TP60.1
/CPU/LCD/P2-VEE: C33.1, P2.30 (VEE), R16.2, R17.1, TP61.1
/CPU/LCD/Q1B: C28.2, Q1.1 (B), R27.2, TP74.1
/CPU/LCD/Q3B: C42.2, Q3.1 (B), TP73.1
/CPU/LCD/U3-COM: TP69.1, U3.4 (COM), U5.2 (B-NPN), U5.5 (B-PNP)
/CPU/LCD/U3-VDD: C2.1, TP63.1, U3.19 (VDD)
/CPU/LCD/U5-3: C33.2, C54.1, TP72.1, U5.3 (C-PNP), U5.6 (C-NPN)
/CPU/LCD/V0: P2.40 (V0), TP64.1, U3.5 (V0)
/CPU/LCD/V1: P2.39 (V1), TP65.1, U3.6 (V1)
/CPU/LCD/V2: P2.38 (V2), TP66.1, U3.14 (V2)
/CPU/LCD/V3: P2.37 (V3), TP67.1, U3.16 (V3)
/CPU/LCD/V4: P2.36 (V4), TP68.1, U3.17 (V4)
/CPU/LCD/VCOM: C54.2, P2.29 (VCOM), Q3.3 (C), TP70.1, VR1.2
/CPU/LCD/VR1-2: R15.1, TP71.1, VR1.1
/CPU/LDB1: P2.23 (B1), TP40.1; also elsewhere on the board
/CPU/LDB2: P2.22 (B2), TP41.1; also elsewhere on the board
/CPU/LDB3: P2.21 (B3), TP42.1; also elsewhere on the board
/CPU/LDB4: P2.20 (B4), TP43.1; also elsewhere on the board
/CPU/LDB5: P2.19 (B5), TP44.1; also elsewhere on the board
/CPU/LDG1: P2.17 (G1), TP45.1; also elsewhere on the board
/CPU/LDG2: P2.16 (G2), TP46.1; also elsewhere on the board
/CPU/LDG3: P2.15 (G3), TP47.1; also elsewhere on the board
/CPU/LDG4: P2.14 (G4), TP48.1; also elsewhere on the board
/CPU/LDG5: P2.13 (G5), TP49.1; also elsewhere on the board
/CPU/LDR1: P2.12 (R1), TP50.1; also elsewhere on the board
/CPU/LDR2: P2.11 (R2), TP51.1; also elsewhere on the board
/CPU/LDR3: P2.10 (R3), TP52.1; also elsewhere on the board
/CPU/LDR4: P2.9 (R4), TP53.1; also elsewhere on the board
/CPU/LDR5: P2.8 (R5), TP54.1; also elsewhere on the board
/CPU/LP: P2.4 (LP), TP56.1; also elsewhere on the board
/CPU/MOD: P2.28 (MOD), TP36.1; also elsewhere on the board
/CPU/PS: P2.5 (PS), TP55.1; also elsewhere on the board
/CPU/REVC: TP62.1, U3.3 (SW); also elsewhere on the board
/CPU/SPL: P2.24 (SPL), TP39.1; also elsewhere on the board
/CPU/SPS: P2.26 (SPS), TP37.1; also elsewhere on the board
/VCNT5: Q2.1 (B); also elsewhere on the board
/VSHD: C14.1, P2.2 (TST1), P2.7 (VSHD), P2.27 (TST3), Q2.3 (C), TP26.1; also elsewhere on the board
GND: C1.2, C2.2, C13.2, C14.2, C58.2, D4.2 (A), P2.0 (AGND), P2.6 (DGND), P2.18 (G0), P2.35 (AGND), Q3.2 (E), R17.2, R27.1, R28.2, U3.12 (GND), U5.1 (E-NPN), VR1.3; also elsewhere on the board
VDD3: Q2.2 (E); also elsewhere on the board
VDD5: C1.1, C13.1, C42.1, P2.34 (VSHA), R15.2, U3.18 (VCC), U5.4 (E-PNP); also elsewhere on the board
VDD13: C28.1, Q1.2 (E); also elsewhere on the board
VDD-15: C32.2, DZ1.2 (A), P2.31 (VSS), R16.1, TP58.1; also elsewhere on the board

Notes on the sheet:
AGB-LCD
